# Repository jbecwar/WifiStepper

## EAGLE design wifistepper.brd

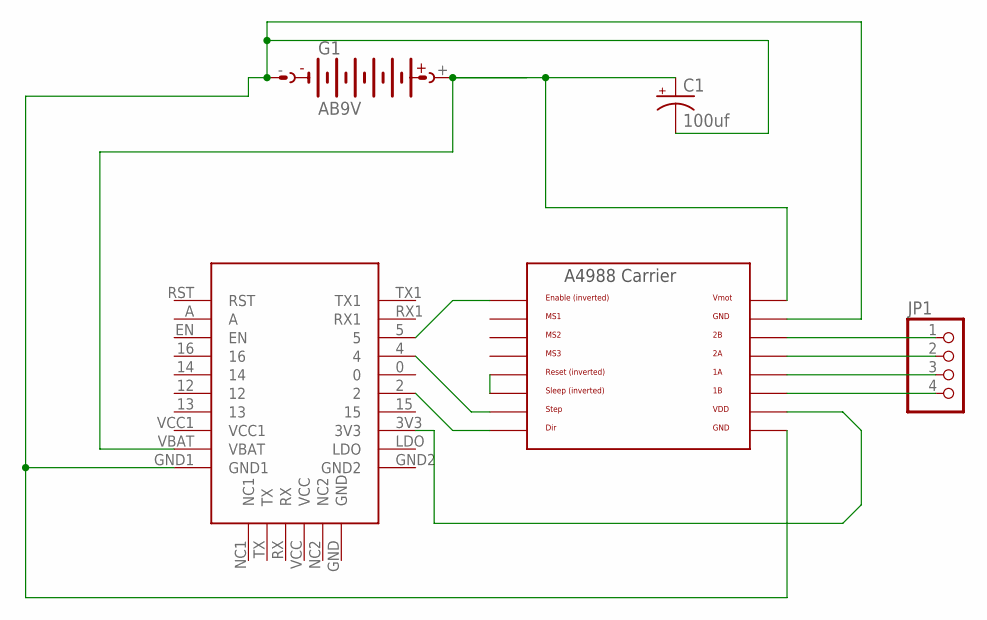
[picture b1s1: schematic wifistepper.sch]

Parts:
C1: 100uf; E2,5-6
G1: AB9V
JP1: PINHD-1X4; 1X04
U$1: HUZZAH_BREAKOUT_ESP8266THROUGHHOLE; HUZZAH_BREAKOUT
U$2: A4988BREAKOUT

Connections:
unnamed: C1.+, G1.+, U$1.VBAT, U$2.VMOT
unnamed: JP1.1, U$2.2B
unnamed: C1.-, G1.-, U$1.GND1, U$2.GND, U$2.GND@0 (GND)
unnamed: JP1.2, U$2.2A
unnamed: JP1.3, U$2.1A
unnamed: JP1.4, U$2.1B
unnamed: U$1.3V3, U$2.VDD
unnamed: U$2.RST, U$2.SLP (SLEEP)
unnamed: U$1.5, U$2.EN
unnamed: U$1.4, U$2.STEP
unnamed: U$1.2, U$2.DIR

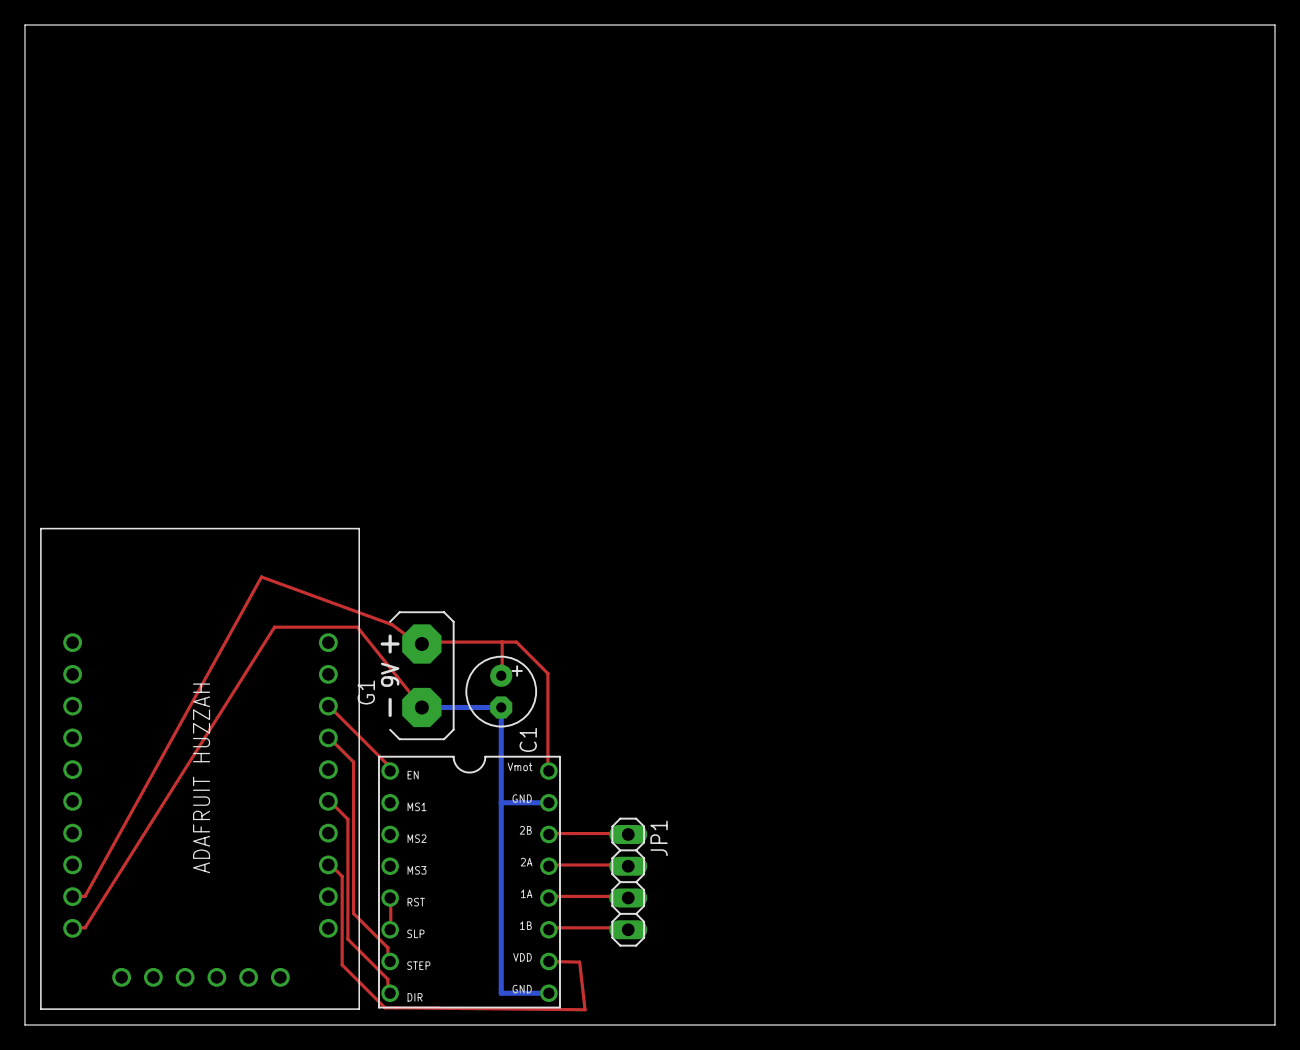
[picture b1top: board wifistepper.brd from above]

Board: 2 copper layers, 100.0 x 80.0 mm, 5 parts (0 on the bottom side), 11 nets.

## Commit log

2016-08-01 Init project.
